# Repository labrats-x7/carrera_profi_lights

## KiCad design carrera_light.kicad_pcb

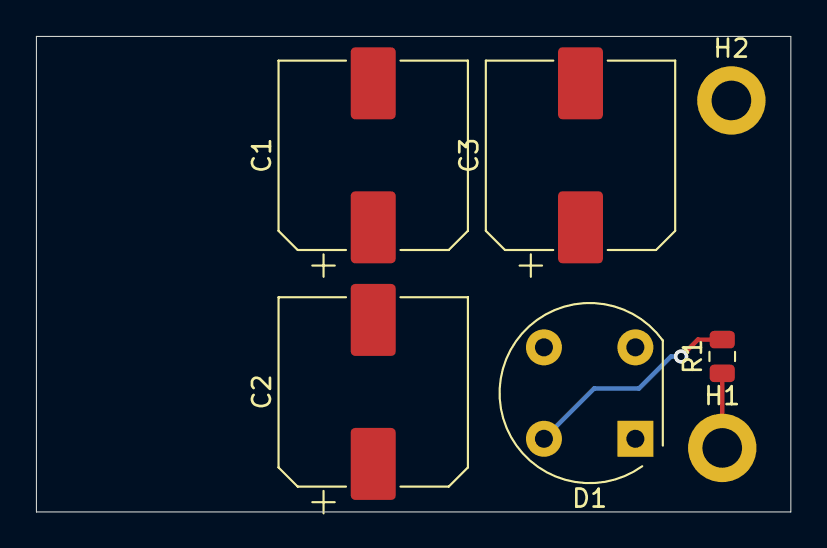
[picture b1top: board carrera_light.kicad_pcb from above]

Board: 2 copper layers, 41.9 x 26.4 mm, 7 parts (0 on the bottom side), 5 nets.

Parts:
C1, C2, C3: CP; CP_Elec_10x10
D1: B40C1500G; Diode_Bridge_Round_D9.8mm
H1, H2: MountingHole_Pad; MountingHole_2.2mm_M2_DIN965_Pad
R1: R18; R_0805_2012Metric

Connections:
+9V: H1.1, R1.1
GND: C1.2, C2.2, C3.2, D1.3
GNDPWR: D1.2, H2.1
unnamed: C1.1, C2.1, C3.1, D1.1
unnamed: D1.4, R1.2

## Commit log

2020-12-29 first parts added
